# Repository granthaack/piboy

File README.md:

PiBoy SP

This board is designed to fit inside of a GBA SP Shell and work in tandem with a SPI LCD Screen and Raspberry Pi Zero to create a portable game console.
https://www.granthaack.com/piboy-sp

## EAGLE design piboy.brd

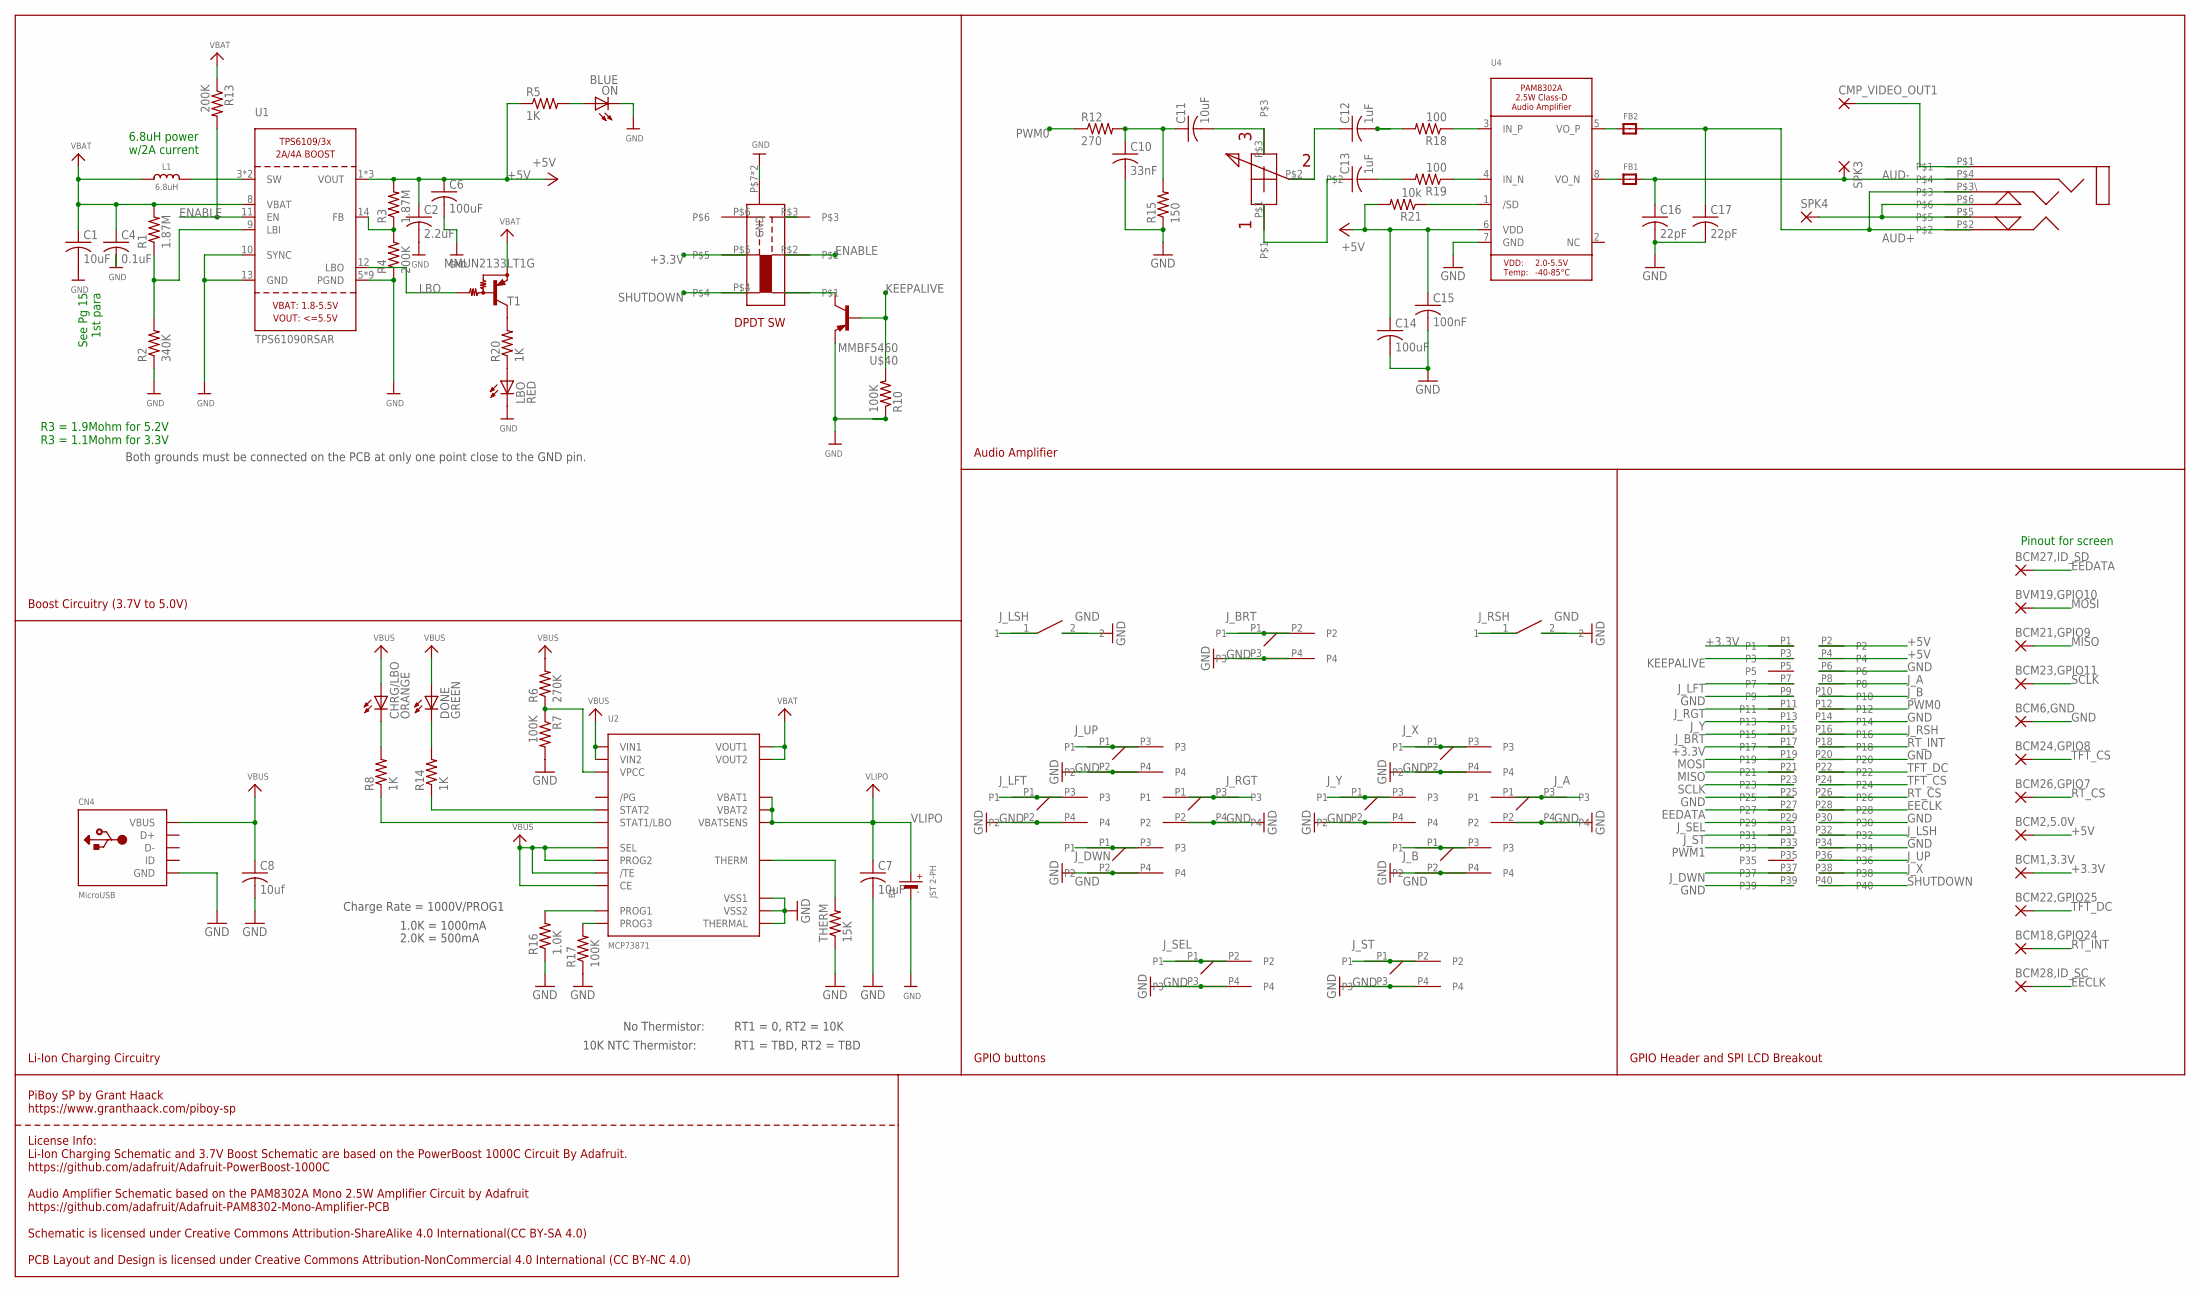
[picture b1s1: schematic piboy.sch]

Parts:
B1: JST 2-PH; MICROBUILDER_JSTPH2_NOTHERMALS
BCM1,3.3V, BCM2,5.0V, BCM6,GND, BCM18,GPIO24, BCM21,GPIO9, BCM22,GPIO25, BCM23,GPIO11, BCM24,GPIO8, BCM26,GPIO7, BCM27,ID_SD, BCM28,ID_SC: WIREPAD_1,6/0,9
BVM19,GPIO10: WIREPAD_1,6/0,9
C1, C7, C11: 10uF; C1210
C2: 2.2uF; C0805
C4: 0.1uF; C0805
C6, C14: 100uF; C1210
C8: 10uf; C0805
C10: 33nF; C0805
C12, C13: 1uF; C0805
C15: 100nF; C0805
C16, C17: 22pF; C0805
CHRG/LBO: ORANGE; ADAFRUIT_CHIPLED_0603
CMP_VIDEO_OUT1: WIREPAD_1,6/0,9
CN4: MicroUSB; 4UCONN_20329
DONE: GREEN; ADAFRUIT_CHIPLED_0603
FB1, FB2: FERRITE0805; 0805
L1: 6.8uH; INDUCTOR_5X5MM_TDK_VLC5045
LBO: RED; ADAFRUIT_CHIPLED_0603
ON: BLUE; ADAFRUIT_CHIPLED_0603
R1, R3: 1.87M; R0805
R2: 340K; R0805
R4, R13: 200K; R0805
R5, R8, R14, R20: 1K; R0805
R6: 270K; R0805
R7, R10, R17: 100K; R0805
R12: 270; R0805
R15: 150; R0805
R16: 1.0K; R0805
R18, R19: 100; R0805
R21: 10k; R0805
SPK3, SPK4: WIREPAD_1,6/0,9
T1: MMUN2133LT1G; TRANSISTOR_SC59-BEC
THERM: 15K; R0805
U1: TPS61090RSAR; PVQFN-16
U2: MCP73871; QFN20_4MM
U4: AUDIOAMP_PAM8302A; MSOP8_0.65MM
U$9: 961240-6300-AR-PR
U$10, U$11, U$12, U$13, U$15, U$16, U$17, U$18: PIBOY_SKRRAAE010
U$21, U$22, U$25: PIBOY_TL3315NF100Q
U$26, U$28: SWITCH_TL1105L-4,3
U$29: RK10J12R0A0B
U$30: SJ-43504-SMT-TR
U$31: EG2210-SW
U$40: MMBF5460; SOT23

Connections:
+3.3V: BCM1,3.3V.1, U$9.P1, U$9.P17, U$31.P$5
+5V: BCM2,5.0V.1, C2.1, C6.1, C14.1, C15.1, R3.2, R5.1, R21.2, U1.1 (VOUT), U1.15 (VOUT), U1.16 (VOUT), U4.6 (VDD), U$9.P2, U$9.P4
AUD+: C17.1, FB2.2, U$30.P$2, U$30.P$3\
AUD+_HDPN_OUT: SPK4.1, U$30.P$5, U$30.P$6
AUD-: C16.1, FB1.2, SPK3.1, U$30.P$4
CMP_VIDEO_OUT1: CMP_VIDEO_OUT1.1, U$30.P$1
EECLK: BCM28,ID_SC.1, U$9.P28
EEDATA: BCM27,ID_SD.1, U$9.P27
ENABLE: R13.2, U1.11 (EN), U$31.P$2
GND: B1.1 (-), B1.NC1 (-), B1.NC2 (-), BCM6,GND.1, C1.2, C2.2, C4.2, C6.2, C7.2, C8.2, C10.2, C14.2, C15.2, C16.2, C17.2, CN4.BASE@1 (GND), CN4.BASE@2 (GND), CN4.GND, CN4.SPRT@1 (GND), CN4.SPRT@2 (GND), CN4.SPRT@3 (GND), CN4.SPRT@4 (GND), LBO.C, ON.C, R2.1, R4.1, R7.2, R10.1, R15.1, R16.1, R17.1, THERM.1, U1.5 (PGND), U1.6 (PGND), U1.7 (PGND), U1.10 (SYNC), U1.13 (GND), U1.P$18 (PGND), U1.P$19 (PGND), U1.P$20 (PGND), U1.P$21 (PGND), U1.P$22 (PGND), U1.THERMAL (PGND), U2.P$10 (VSS1), U2.P$11 (VSS2), U2.P$21 (THERMAL), U4.7 (GND), U$9.P6, U$9.P9, U$9.P14, U$9.P20, U$9.P25, U$9.P30, U$9.P34, U$9.P39, U$10.P2, U$10.P4, U$11.P2, U$11.P4, U$12.P2, U$12.P4, U$13.P2, U$13.P4, U$15.P2, U$15.P4, U$16.P2, U$16.P4, U$17.P2, U$17.P4, U$18.P2, U$18.P4, U$21.P3, U$21.P4, U$22.P3, U$22.P4, U$25.P3, U$25.P4, U$26.2, U$28.2, U$31.P$7 (GND), U$31.P$8 (GND), U$40.2 (S)
J_A: U$9.P8, U$17.P1, U$17.P3
J_B: U$9.P10, U$18.P1, U$18.P3
J_BRT: U$9.P15, U$25.P1, U$25.P2
J_DWN: U$9.P37, U$13.P1, U$13.P3
J_LFT: U$9.P7, U$11.P1, U$11.P3
J_LSH: U$9.P32, U$26.1
J_RGT: U$9.P11, U$12.P1, U$12.P3
J_RSH: U$9.P16, U$28.1
J_SEL: U$9.P29, U$21.P1, U$21.P2
J_ST: U$9.P31, U$22.P1, U$22.P2
J_UP: U$9.P36, U$10.P1, U$10.P3
J_X: U$9.P38, U$15.P1, U$15.P3
J_Y: U$9.P13, U$16.P1, U$16.P3
KEEPALIVE: R10.2, U$9.P3, U$40.3 (G)
LBO: T1.B, U1.12 (LBO)
MISO: BCM21,GPIO9.1, U$9.P21
MOSI: BVM19,GPIO10.1, U$9.P19
unnamed: L1.P$2 (2), U1.3 (SW), U1.4 (SW)
unnamed: LBO.A, R20.1
unnamed: R1.1, R2.2, U1.9 (LBI)
unnamed: ON.A, R5.2
unnamed: R3.1, R4.2, U1.14 (FB)
unnamed: R20.2, T1.C
unnamed: R6.1, R7.1, U2.P$2 (VPCC)
unnamed: DONE.C, R14.2
unnamed: R14.1, U2.P$7 (STAT2)
unnamed: THERM.2, U2.P$5 (THERM)
unnamed: R8.1, U2.P$8 (STAT1/LBO)
unnamed: CHRG/LBO.C, R8.2
unnamed: R17.2, U2.P$12 (PROG3)
unnamed: R16.2, U2.P$13 (PROG1)
unnamed: C10.1, C11.1, R12.2, R15.2
unnamed: U$31.P$1, U$40.1 (D)
unnamed: C11.2, U$29.P$3
unnamed: C12.1, U$29.P$2
unnamed: C13.1, U$29.P$1
unnamed: C13.2, R19.2
unnamed: C12.2, R18.2
unnamed: R18.1, U4.3 (IN_P)
unnamed: R19.1, U4.4 (IN_N)
unnamed: R21.1, U4.1 (/SD)
unnamed: FB1.1, U4.8 (VO_N)
unnamed: FB2.1, U4.5 (VO_P)
PWM0: R12.1, U$9.P12
PWM1: U$9.P33
RT_CS: BCM26,GPIO7.1, U$9.P26
RT_INT: BCM18,GPIO24.1, U$9.P18
SCLK: BCM23,GPIO11.1, U$9.P23
SHUTDOWN: U$9.P40, U$31.P$4
TFT_CS: BCM24,GPIO8.1, U$9.P24
TFT_DC: BCM22,GPIO25.1, U$9.P22
VBAT: C1.1, C4.1, L1.P$1 (1), R1.2, R13.1, T1.E, U1.8 (VBAT), U2.P$1 (VOUT1), U2.P$20 (VOUT2)
VBUS: C8.1, CHRG/LBO.A, CN4.VBUS, DONE.A, R6.2, U2.P$3 (SEL), U2.P$4 (PROG2), U2.P$9 (/TE), U2.P$17 (CE), U2.P$18 (VIN1), U2.P$19 (VIN2)
VLIPO: B1.2 (+), C7.1, U2.P$14 (VBAT1), U2.P$15 (VBAT2), U2.P$16 (VBATSENS)

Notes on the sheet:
Both grounds must be connected on the PCB at only one point close to the GND pin.
See Pg 15 1st para
6.8uH power w/2A current
R3 = 1.9Mohm for 5.2V R3 = 1.1Mohm for 3.3V
Charge Rate = 1000V/PROG1
1.0K = 1000mA
2.0K = 500mA
No Thermistor:
10K NTC Thermistor:
RT1 = 0, RT2 = 10K
RT1 = TBD, RT2 = TBD
Pinout for screen
GPIO Header and SPI LCD Breakout
GPIO buttons
Boost Circuitry (3.7V to 5.0V)
Li-Ion Charging Circuitry
Audio Amplifier
License Info: Li-Ion Charging Schematic and 3.7V Boost Schematic are based on the PowerBoost 1000C Circuit By Adafruit. https://github.com/adafruit/Adafruit-PowerBoost-1000C Audio Amplifier Schematic based on the PAM8302A Mono 2.5W Amplifier Circuit by Adafruit https://github.com/adafruit/Adafruit-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
PiBoy SP by Grant Haack https://www.granthaack.com/piboy-sp

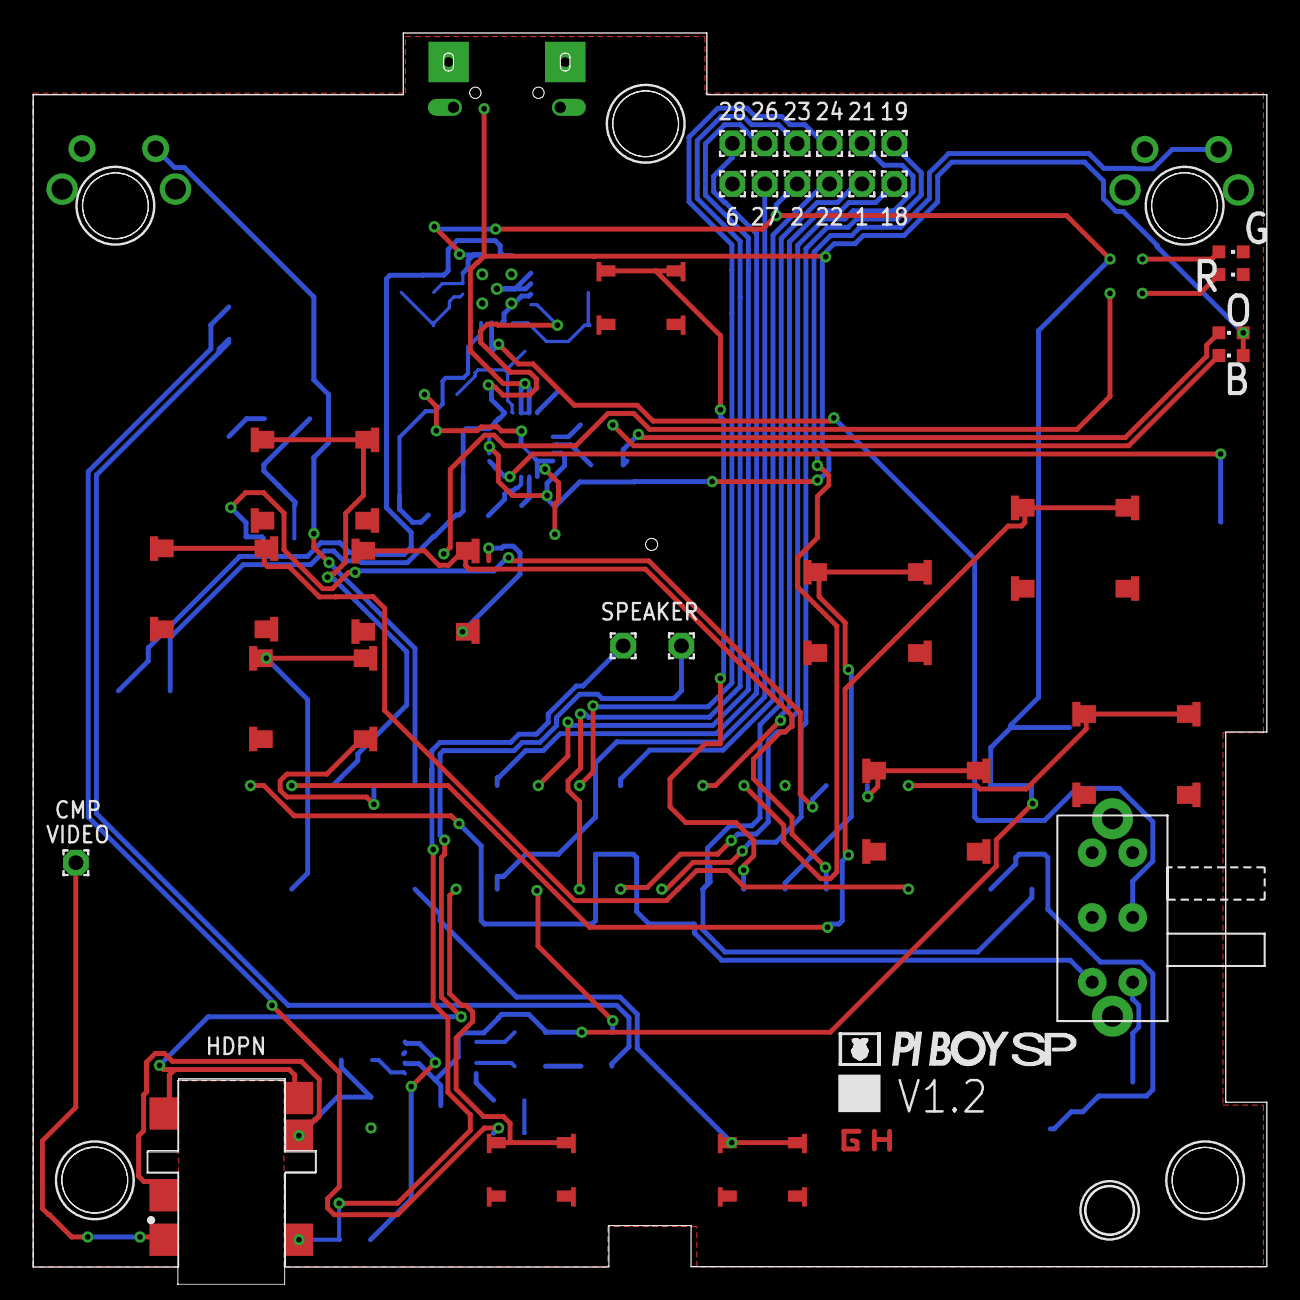
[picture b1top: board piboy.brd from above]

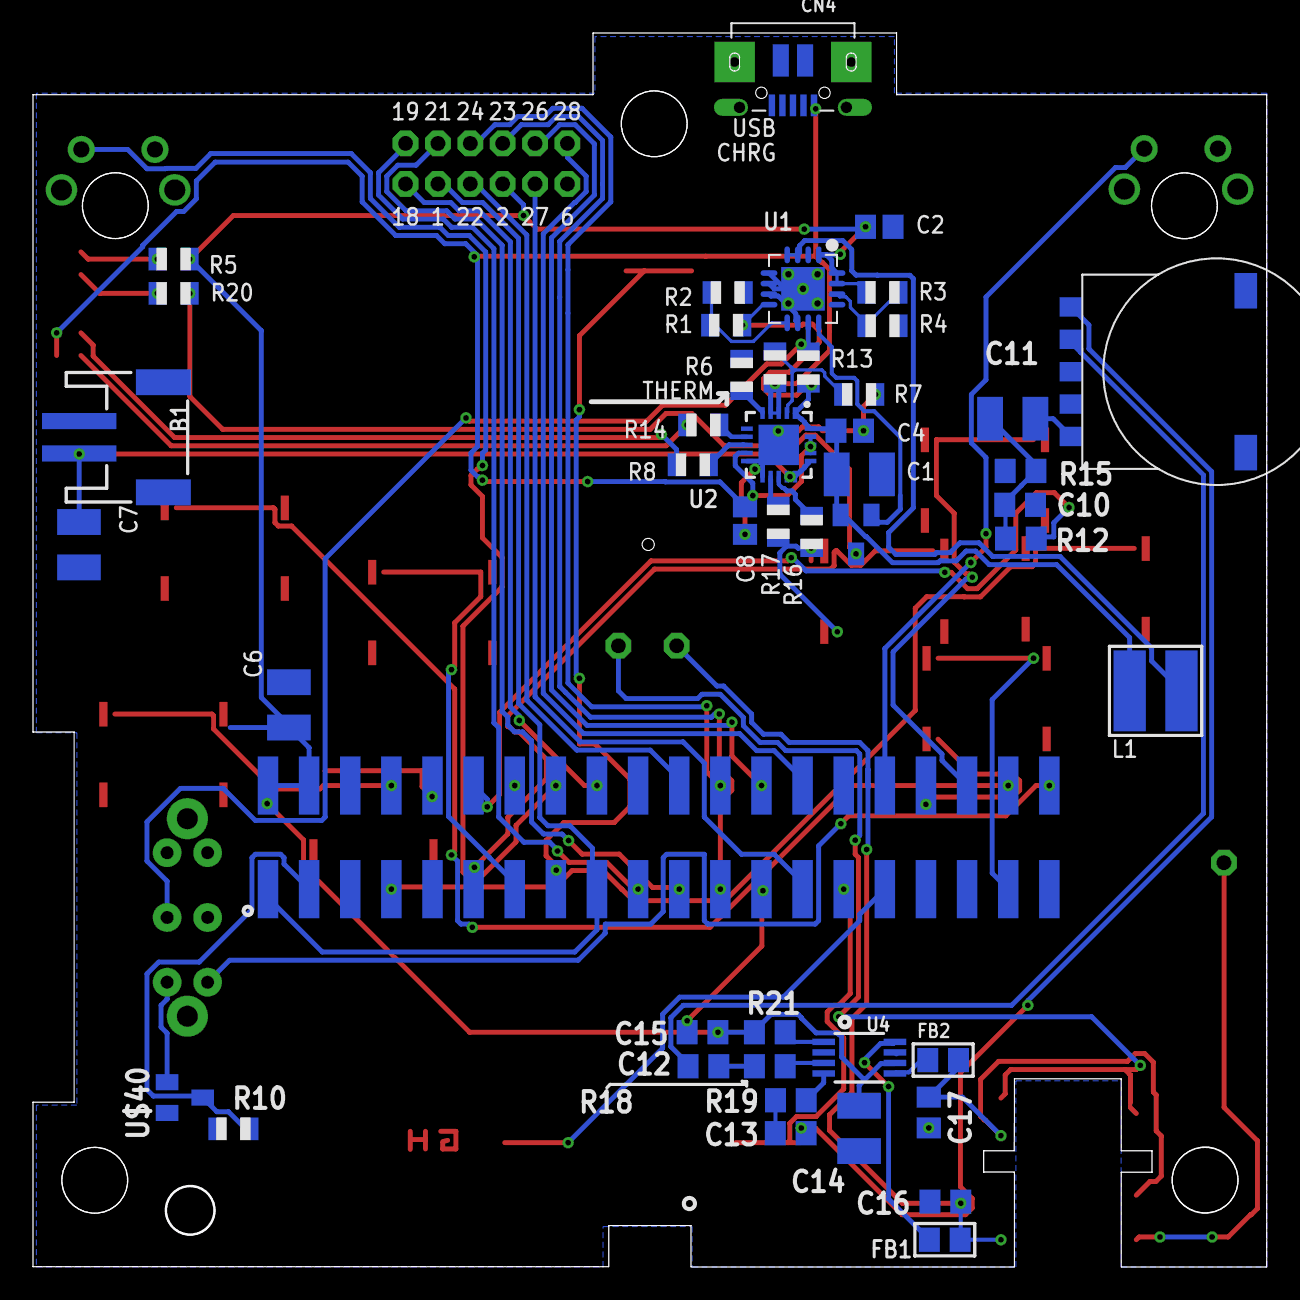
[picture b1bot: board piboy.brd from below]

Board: 2 copper layers, 76.2 x 76.2 mm, 80 parts (46 on the bottom side), 63 nets.

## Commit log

2017-05-10 -first commit
2017-06-07 -added other drawings of the layout -started to lay out the components on the board
2017-06-07 -added traces -performed a DRC, no overlaps found
2017-06-07 -whoops forgot to save
2017-06-07 -added cutout for the mid mount headphone jack
2017-06-08 -went through drc
2017-06-12 TODO: edit device packages to remove silkscreen
2017-06-12 -removed all problematic silkscreen -exported all parts into a new library, piboy_new.lbr TODO: Rename piboy_new.lbr
2017-07-03 -redid audio circuit -moved around components on the board -began silkscreen -cleared clearance, overlap, airwire DRC -checked component values
2017-07-03 -finished silkscreen -done before copper pours
2017-07-03 -performed copper ground pours
2017-07-03 -fixed layer on the volume knob
2017-07-04 renamed branch to reflect trace size will be redoing with thicker traces
2017-07-04 -moved around components
2017-07-04 -applied oshpark's DRC file -moved components around
2017-07-04 -finished traces
2017-07-05 -fixed problem with PAM8302 having the wrong pins -finished routing with 8mil traces and 8mil spacing -performed ground pours -finished basic silkscreen -double checked pin assignments on chips -drc 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
2017-07-05 -added fancy logo for screenprint
2017-07-05 -added LED silkscreen that I forgot
2017-07-05 -fixed fancy silkscreen
2017-07-05 -fixed fancy silkscreen again
2017-07-05 -fixed SO-8 package on the PAM8302
2017-07-05 -tiny change to the silkscreen because I'm obsessive
2017-07-05 -slight placement modifications on the power switch and the battery port
2017-07-05 -more small position tweaks
2017-07-05 -small changes
2017-07-05 -added drills for mounting holes
2017-07-05 -moved headphone jack down by 5 mm to make it easier to plug in
2017-07-22 -connected IN- in amp input to ground
2017-08-09 -Created a new board revision 1.1 -moved layout of the screen pins -relocated the audio circuit
    TODO
    -Relocate the power circuit
    -Fix the button smd pads
2017-08-09 -routed power circuit -routed SPI pinouts TODO -Clean up schematic: replace parts with parts that have labels, replace similar parts with all parts from the same library
2017-08-31 -*finally* think I solved the audio issue, redid audio schematic with new parts -started layout
2017-09-01 -routed all signals before using the autorouter for voltages and GND
2017-09-01 -TODO: Fix the buttons so they work with the ground plane -Fix the small buttons so they have large enough solder pads
2017-09-01 -fixed small button pads
2017-09-01 -fixed ground plane issue
2017-09-01 -DRC passed -TODO:Make sure all the GPIO pins I have wired up as buttons can actually act as buttons
2017-09-01 -DRC Passed -Modified ground plane, made better -TODO silkscreen for audio circuit
2017-09-01 -fixed silkscreen -added yotsuba pcb art
2017-09-02 -added a dummy pin to the programming header so a standard 6 pin female connector will fit -slight silkscreen changes
2018-03-23 -fixed GPIO issues TODO Redo the audio circuit with PAM8302 and high pass filter
2018-03-23 -finished the PAM8302A audio amp
2018-03-24 -did some wiring
2018-03-26 -performed a DRC, no errors TODO fix silkscreen layers clean up wires
2018-03-27 -added license info on the schematic
2018-03-27 -corrected license info
2018-03-29 -added safe shutdown circuit

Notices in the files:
piboy.brd:
PCB Layout and Design is licensed under
Creative Commons
Attribution-NonCommercial 4.0
International (CC BY-NC 4.0)
piboy.sch:
Schematic is licensed under Creative Commons Attribution-ShareAlike 4.0 International(CC BY-SA 4.0)
PCB Layout and Design is licensed under Creative Commons Attribution-NonCommercial 4.0 International (CC BY-NC 4.0)
parts and their libraries:
microbuilder: This work is placed in the public domain, and may be freely used for commercial and non-commercial work with the following conditions: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
